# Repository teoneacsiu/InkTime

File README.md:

# InkTime

Smartwatch open-source bazat pe **nRF52840**, proiectat pentru cursul TSC. Acest repository contine partea de hardware, manufacturing si integrare mecanica pentru varianta **InkTime**.

---

## Structura repository-ului

```text
Hardware/
  - schematic (.sch)
  - board (.brd)

Manufacturing/
  - gerbers.zip
  - Bill of Materials (.bom / .csv)
  - Pick and Place (.cpl)

Mechanical/
  - ansamblu complet (.step)
  - fisierul Fusion360 al ansamblului complet

Images/
  - randari PCB
  - randari assembly
  - capturi schematic / board

LICENSE
README.md
```

---

## Stare proiect

- [x] structura repo
- [x] README completat
- [x] BOM de documentatie pentru componentele critice
- [x] schematic complet
- [x] ERC curat
- [x] board complet
- [x] DRC cu fisierul oficial
- [x] gerbers / BOM / CPL exportate
- [ ] model 3D complet: PCB + baterie + display + shaker + carcasa
- [ ] review DVT
- [ ] fix-uri pentru GNG

---

## Block diagram

```mermaid
flowchart LR
    USB[USB-C]
    ESD[USB ESD Protection]
    PMIC[BQ25180YBGR\nLi-Ion Charger + Power Path]
    DCDC[RT6160AWSC\nBuck-Boost 3V3]
    MCU[nRF52840\nBLE SoC]
    IMU[BMA421/BMA423\nAccelerometer]
    FG[MAX17048G+T10\nFuel Gauge]
    HAPTIC[DRV2605YZFR\nHaptic Driver]
    EPDPWR[E-Paper Power Stage]
    EPD[24-pin E-Paper FPC]
    BTN[3 Buttons]
    SWD[SWD Header / Test Pads]
    ANT[2.4 GHz Chip Antenna]
    BAT[Li-Po Battery]

    USB --> ESD --> MCU
    USB --> PMIC
    BAT --> PMIC
    BAT --> FG
    PMIC --> DCDC
    DCDC --> MCU
    DCDC --> IMU
    DCDC --> FG
    DCDC --> HAPTIC
    DCDC --> EPDPWR
    MCU <-->|I2C| IMU
    MCU <-->|I2C| PMIC
    MCU <-->|I2C| FG
    MCU <-->|I2C| HAPTIC
    MCU -->|SPI + control| EPDPWR
    EPDPWR --> EPD
    MCU --> BTN
    MCU --> SWD
    MCU --> ANT
```

---

## Arhitectura hardware

### 1. Microcontroller + radio
Controllerul principal este **nRF52840** in capsula QFN/AQFN, folosit pentru:
- controlul intregului sistem;
- comunicare BLE;
- interfata USB;
- I2C pentru PMIC / IMU / fuel gauge / haptic;
- SPI + semnale de control pentru display-ul e-paper;
- SWD pentru debug si programare.

Blocul radio foloseste:
- cristal de **32 MHz** pentru radio;
- cristal de **32.768 kHz** pentru timp real / low power;
- retea de adaptare RF;
- antena chip **2450AT18B100E**.

### 2. Alimentare
Alimentarea este impartita in doua etape:
- **BQ25180YBGR** pentru incarcarea bateriei Li-Po si power-path;
- **RT6160AWSC** pentru generarea tensiunii principale de **3V3**.

Aceasta separare permite:
- alimentare din USB;
- incarcare baterie;
- distributie stabila de 3V3 pentru MCU si periferice.

### 3. Senzori si periferice
- **BMA421/BMA423** - accelerometru low-power pentru detectie miscare / gesturi;
- **MAX17048G+T10** - fuel gauge pentru estimarea starii bateriei;
- **DRV2605YZFR** - driver haptic pentru feedback tactil;
- **E-paper connector + drive stage** - interfata catre display-ul principal;
- **3 butoane** - interfata fizica utilizator;
- **USB-C + ESD** - alimentare si comunicare USB.

---

## Interfete si mapare pini nRF52840

| Functie | Net / semnal | Pin nRF52840 | Motiv |
|---|---|---:|---|
| I2C data | SDA | P0.06 | magistrala comuna pentru PMIC, IMU, fuel gauge, haptic |
| I2C clock | SCL | P0.07 | magistrala comuna pentru PMIC, IMU, fuel gauge, haptic |
| PMIC interrupt | PMIC_INT | P0.11 | evenimente incarcare / power-path |
| IMU interrupt 1 | IMU_INT1 | P0.08 | semnal de intrerupere de la accelerometru |
| IMU interrupt 2 | IMU_INT2 | P1.08 | al doilea semnal de intrerupere de la accelerometru |
| Haptic enable / trigger | HAPTIC_EN | P0.12 | controlul driverului DRV2605 |
| Fuel gauge alert | ALERT | P0.10 / NFC2 | semnal alerta baterie / SOC |
| USB VBUS detect | VBUS | VBUS pin dedicat | detectare prezenta USB |
| USB data minus | D- | D- pin dedicat | USB 2.0 |
| USB data plus | D+ | D+ pin dedicat | USB 2.0 |
| Display chip select | EPD_CS | P0.05 | selectare SPI pentru e-paper |
| Display data/command | EPD_DC | P0.15 | diferentiere date/comenzi |
| Display busy | EPD_BUSY | P0.16 | status busy din display |
| Display reset | EPD_RST | P0.17 | reset hardware display |
| User button UP | SW_UP | P1.15 | input utilizator |
| User button ENTER | SW_ENT | P0.14 | input utilizator |
| User button DOWN | SW_DN | P1.02 | input utilizator |
| E-paper power enable | GPIO pentru Q1 | P1.01 | comanda alimentarea blocului e-paper |
| SWD data | SWDIO | SWDIO pin dedicat | debug/programare |
| SWD clock | SWDCLK | SWDCLK pin dedicat | debug/programare |
| Trace / debug | SWO | GPIO debug | punct de test pentru debugging |

### Observatii pe maparea pinilor
- Magistrala **I2C** este comuna si reduce numarul total de pini ocupati.
- Interfata USB foloseste pinii dedicati ai nRF52840 pentru compatibilitate corecta.
- Semnalele catre e-paper sunt separate intre control (`EPD_CS`, `EPD_DC`, `EPD_RST`, `EPD_BUSY`) si alimentare.
- Butoanele sunt conectate pe GPIO-uri separate pentru tratare simpla in firmware.
- Semnalele de debug sunt expuse atat prin conectorul SWD, cat si prin test pad-uri.

---

## Functionalitatea fiecarui bloc

### nRF52840
- MCU principal;
- BLE;
- USB FS;
- interfete I2C / SPI / GPIO;
- control low-power.

### BQ25180YBGR
- incarcare baterie Li-Ion/LiPo;
- power-path management;
- monitorizare si configurare prin I2C.

### RT6160AWSC
- buck-boost I2C-programmable;
- genereaza 3V3 din sursa sistemului;
- mentine tensiunea stabila pentru subsisteme.

### BMA421/BMA423
- accelerometru digital ultra-low-power;
- detectare miscare / activitate;
- intreruperi dedicate catre MCU.

### MAX17048G+T10
- fuel gauge pentru baterie LiPo;
- masoara tensiunea si estimeaza state-of-charge;
- alerta low battery catre MCU.

### DRV2605YZFR
- driver haptic pentru actuator ERM/LRA;
- controlabil prin I2C;
- permite feedback tactil complex.

### USB-C + ESD
- alimentare si date USB;
- rezistente de configurare CC;
- protectie ESD pe D+/D-/VBUS.

### E-paper drive + connector
- conector FPC de 24 pini;
- etapa de alimentare si comanda pentru display;
- linii SPI/control catre MCU.

---

## BOM de documentatie

BOM-ul de mai jos contine **componentele critice**. Pentru BOM-ul complet de productie trebuie folosit exportul din Fusion/EAGLE.

| RefDes | Componenta | MPN | Qty | Observatii |
|---|---|---|---:|---|
| U1 | BLE SoC | NRF52840-QIAA-R / QIAA-T | 1 | MCU principal |
| IC1 | Charger + power path | BQ25180YBGR | 1 | management baterie |
| IC9 | Buck-boost converter | RT6160AWSC | 1 | 3V3 principal |
| IC3 | IMU | BMA421 / BMA423 | 1 | biblioteca folosita contine BMA423 |
| U3 | Fuel gauge | MAX17048G+T10 | 1 | monitorizare baterie |
| IC2 | Haptic driver | DRV2605YZFR | 1 | control vibratii |
| J4 | USB-C | KH-TYPE-C-16P | 1 | alimentare + USB |
| D3 | ESD USB | USBLC6-2SC6Y | 1 | protectie D+/D-/VBUS |
| J1 | E-paper FPC | 503480-2400 | 1 | conector display |
| ANT1 | Chip antenna 2.4 GHz | 2450AT18B100E | 1 | BLE antenna |
| J2 | SWD header | TC2030-IDC | 1 | programare / debug |
| D2,D4,D5 | Schottky diode | MBR0530 | 3 | bloc power e-paper |
| Q3 | N-MOS | SI1308EDL-T1-GE3 | 1 | drive e-paper |
| Q1 | P-MOS | DMG2305UX-7 | 1 | comutare alimentare e-paper |
| X1 | RF crystal | 32MHz | 1 | ceas radio |
| X2 | RTC crystal | 32.768kHz | 1 | low-power timing |
| L7 | Inductor DCDC | FTC252012SR47MBCA | 1 | buck-boost RT6160 |
| SW_UP, SW_ENT, SW_DN | Butoane tactile | TBD | 3 | verificare finala dupa layout |
| Battery | Li-Po battery | TBD | 1 | model 3D de desenat |
| Display | E-paper module | TBD | 1 | model 3D de desenat |
| Shaker | ERM/LRA actuator | TBD | 1 | model 3D de desenat |

### Observatii BOM
- Toate rezistentele sunt SMD 0201.
- Toate condensatoarele cu valori `<= 100nF` sunt SMD 0201.
- Condensatoarele cu valori `> 100nF` sunt 0402, cu exceptiile specificate explicit in schema.
- BOM-ul din README este un BOM de documentatie; BOM-ul final de productie va fi exportat direct din CAD.

---

## Design rules si constrangeri care trebuie respectate

### PCB / mechanical
- grosime PCB: **1.0 mm**;
- componentele se amplaseaza **exclusiv pe TOP**;
- rutarea poate fi pe TOP si BOTTOM;
- trebuie **plan de masa pe TOP si pe BOTTOM**;
- daca se folosesc 4 straturi, unul dintre straturile interne trebuie sa fie GND;
- PCB-ul trebuie sa intre in carcasa furnizata;
- USB-C, butoanele si conectorul display trebuie aliniate mecanic cu carcasa.

### RF
- antena trebuie plasata spre exteriorul placii;
- sub antena **nu se pune plan de masa**;
- sub antena **nu se routeaza semnale**;
- se recomanda via stitching in jurul planurilor de GND, in special in zona radio.

### Routing
- trasee de putere: **0.30 mm**;
- trasee de semnal: **minim 0.15 mm**;
- fara unghiuri de 90°;
- se evita vias pe traseele de putere, pe cat posibil;
- condensatoarele de 100nF trebuie puse cat mai aproape de pinii de alimentare.

### Verificari
- ERC obligatoriu;
- DRC obligatoriu cu fisierul de reguli din arhiva;
- eroarea **Only INPUT pins on NET ID** poate fi ignorata;
- erorile de **Dimension** cauzate de butoane si USB pot fi justificate conform cerintei.

### Silkscreen
- silkscreen-ul trebuie sa fie lizibil;
- pe silkscreen se pastreaza **numele componentelor**, nu valorile;
- test pad-urile trebuie marcate clar cu numele semnalelor.

---

## Packaging si reguli de selectie a pasivelor

Conform cerintei:
- toate rezistentele sunt SMD **0201**;
- condensatoarele cu valori **<= 100nF** sunt **0201**;
- condensatoarele cu valori **> 100nF** sunt **0402**, cu exceptiile specificate explicit in schema.

---

## Manufacturing outputs

La final, repository-ul trebuie sa contina:

### Hardware
- `InkTime.sch`
- `InkTime.brd`

### Manufacturing
- `gerbers.zip`
- `InkTime.bom` / `BOM.csv`
- `InkTime.cpl`

### Mechanical
- ansamblu complet `STEP`
- fisierul Fusion360 al ansamblului complet

### Images
- randare PCB top
- randare PCB bottom
- randare assembly complet
- capturi schematic / board

---

## Design log / decizii

### Decizii luate pana acum
- biblioteca utilizata: `InkTime_v5.lbr`;
- schema este implementata dupa modelul furnizat;
- pentru IMU se foloseste simbolul / footprint-ul disponibil in biblioteca (**BMA423**), urmand sa fie mentionat explicit in review si in BOM;
- BOM-ul din README este unul de documentatie; BOM-ul final de asamblare va fi exportat direct din CAD;
- retelele critice de alimentare si RF au fost pastrate compacte pentru a facilita routarea si respectarea constrangerilor de layout.

### Probleme / aspecte de urmarit
- verificarea disponibilitatii finale la JLC pentru toate componentele critice;
- confirmarea exacta a modelului de baterie, display si shaker;
- verificarea finala a footprint-urilor pentru componentele foarte mici (WLCSP / DSBGA / AQFN);
- justificarea eventualelor erori DRC/Dimension acceptate conform cerintei;
- completarea integrarii mecanice 3D a bateriei, display-ului si actuatorului haptic.

---

## Imagini

Imaginile finale vor fi puse in `Images/`:
- `pcb_top.png`
- `pcb_bottom.png`
- `assembly_render.png`
- `schematic_page1.png`
- `schematic_page2.png`

---

## Limitari curente

In momentul actual, partea de proiectare electrica si de PCB este considerata finalizata la nivel de documentatie, iar partea ramasa de completat este integrarea 3D completa:
- modelul 3D al bateriei;
- modelul 3D al display-ului e-paper;
- modelul 3D al shaker-ului;
- verificarea finala a ansamblului complet in carcasa.

Toate celelalte livrabile hardware si de manufacturing sunt pregatite la nivel de repository si documentatie.

---

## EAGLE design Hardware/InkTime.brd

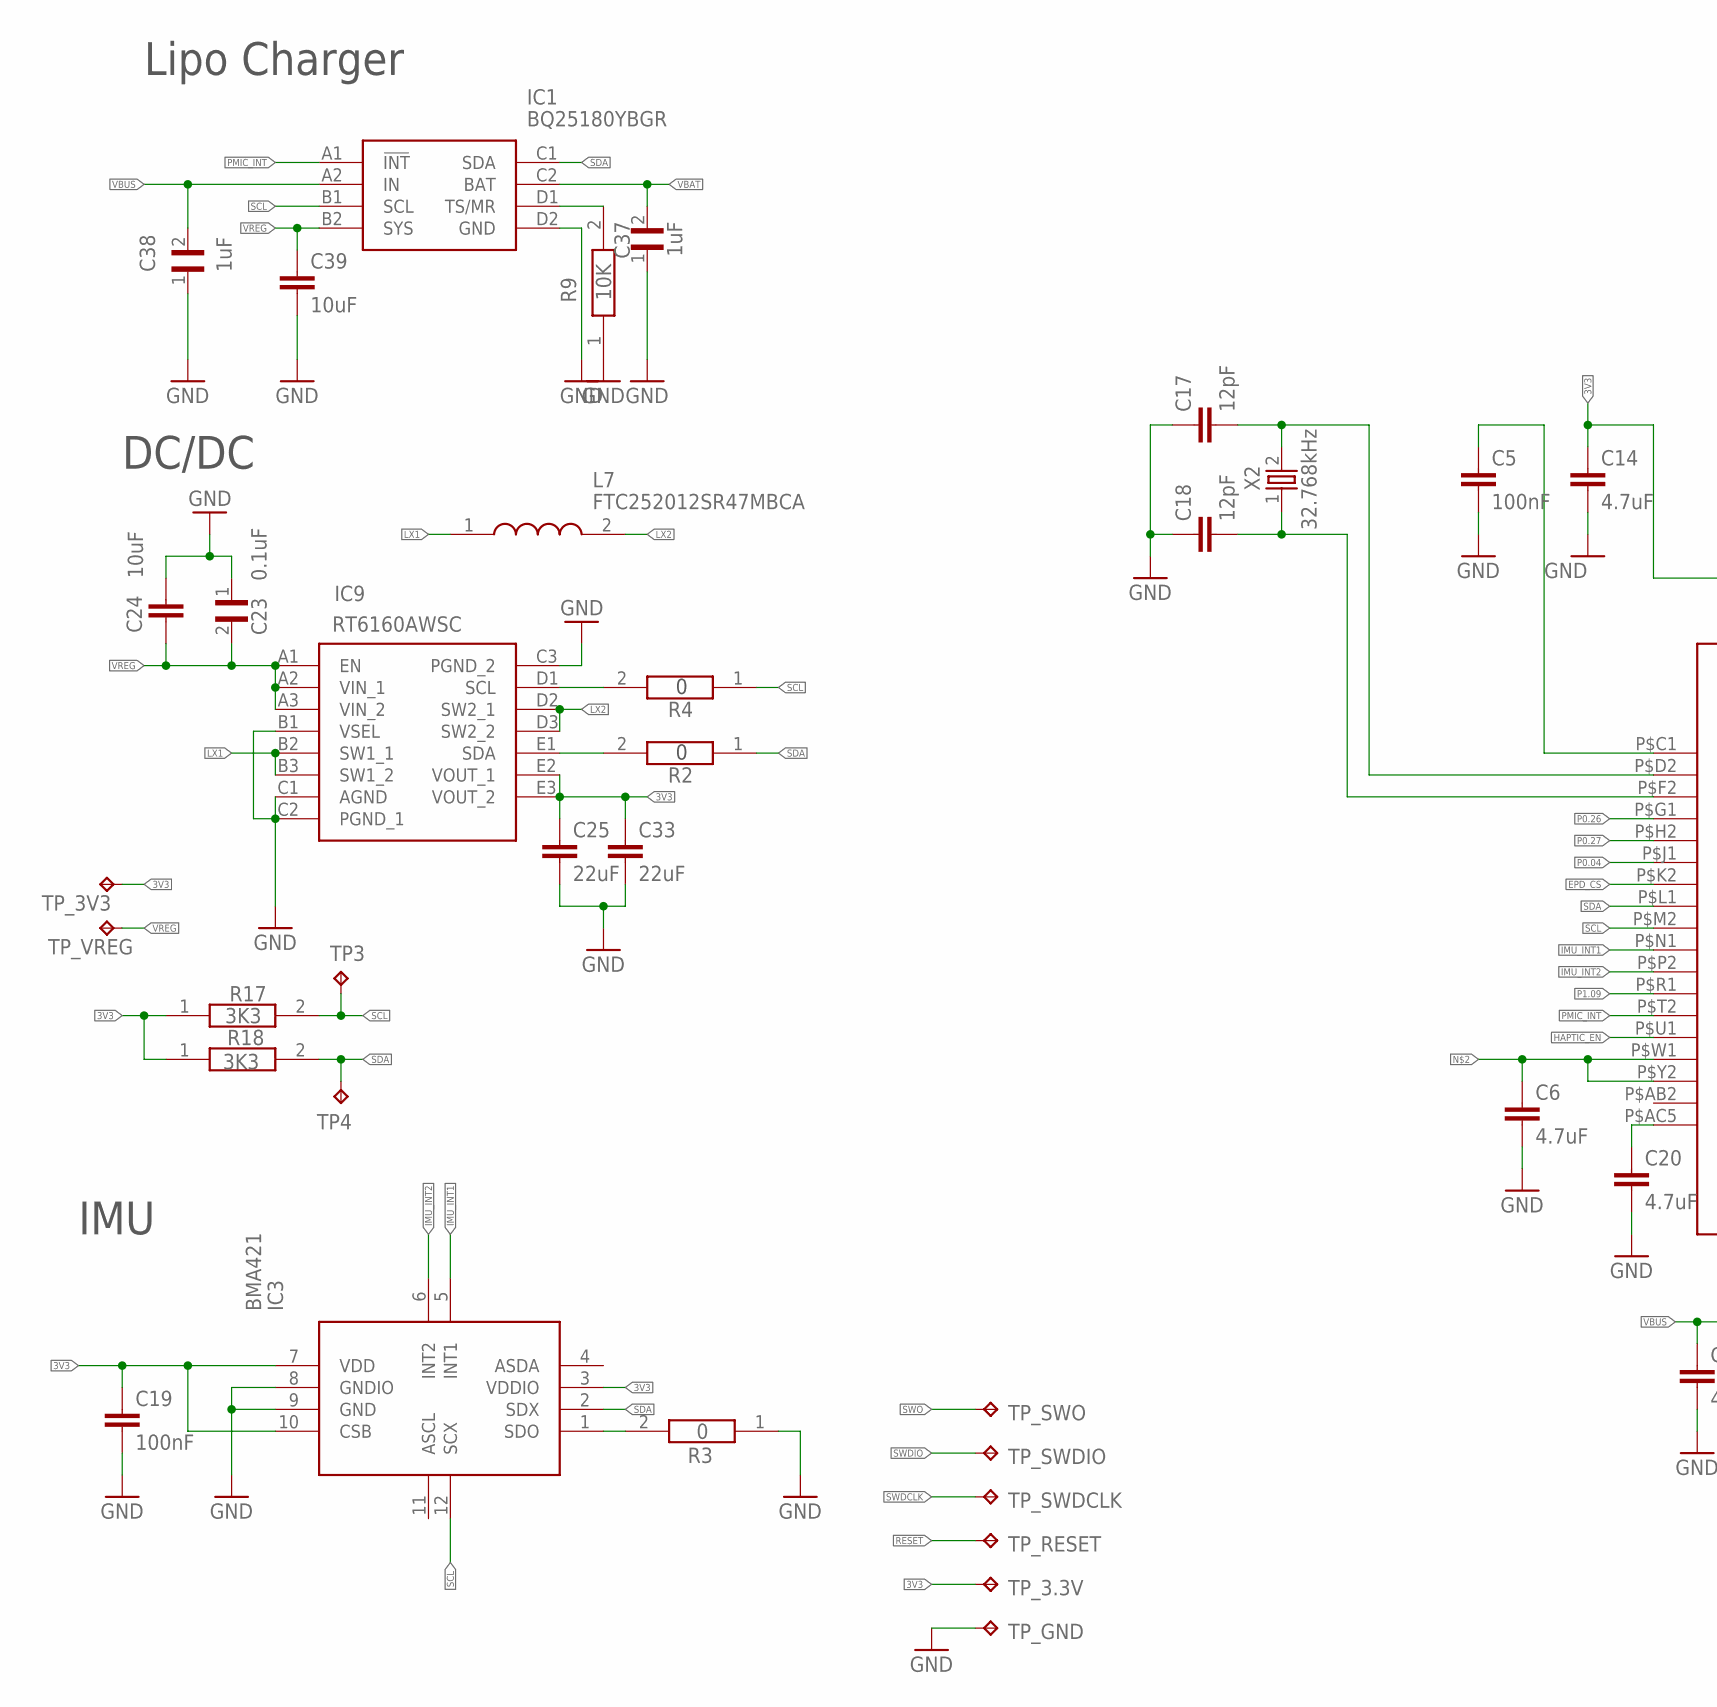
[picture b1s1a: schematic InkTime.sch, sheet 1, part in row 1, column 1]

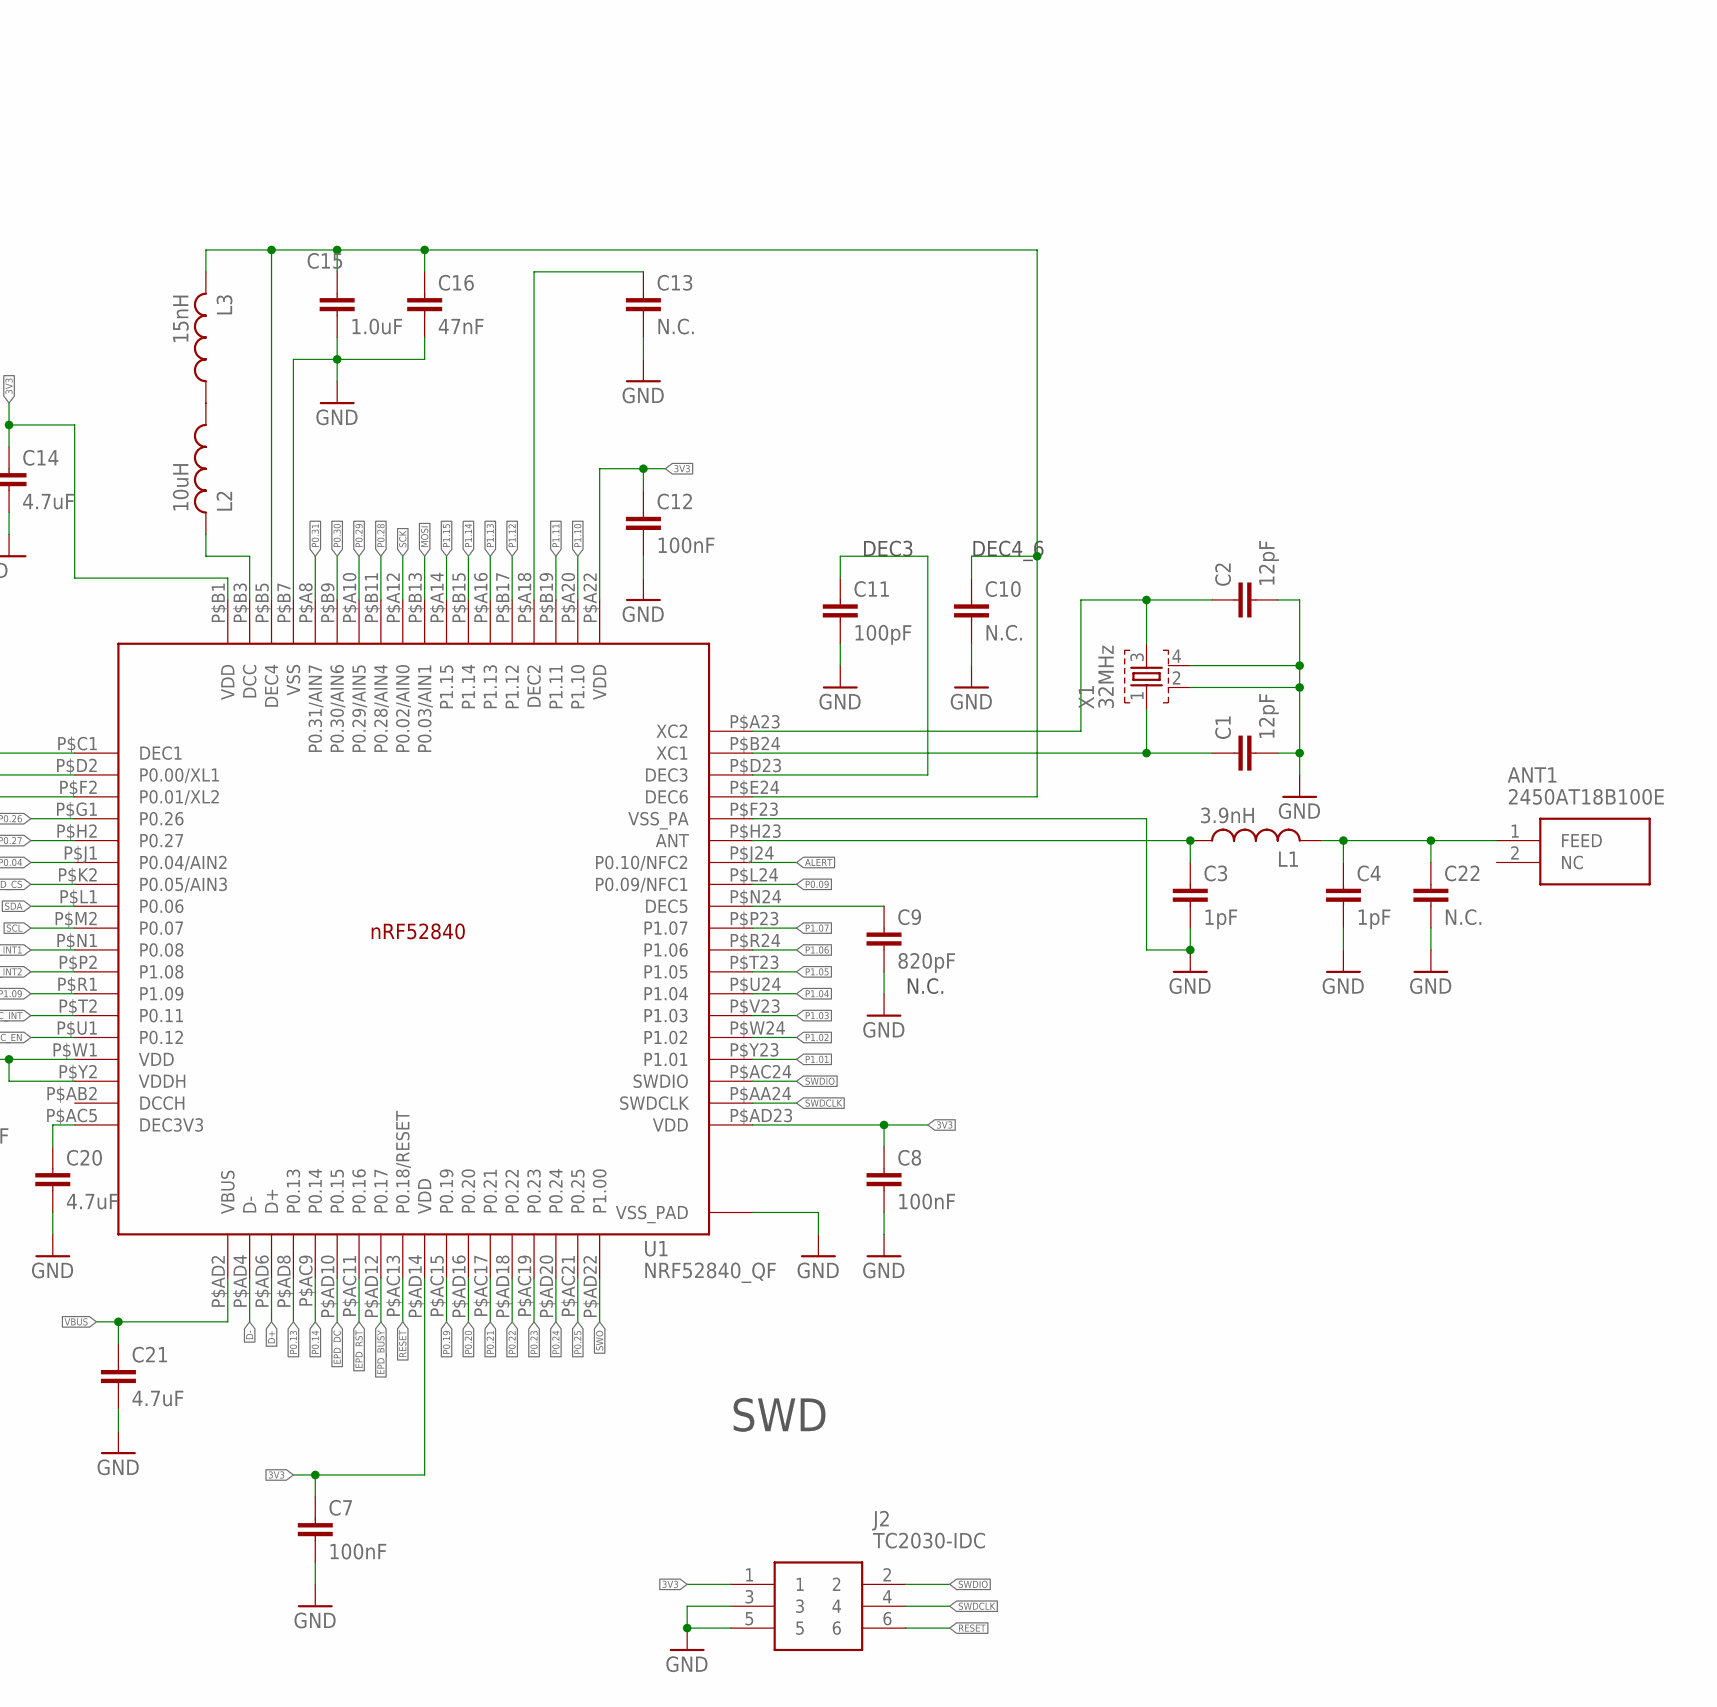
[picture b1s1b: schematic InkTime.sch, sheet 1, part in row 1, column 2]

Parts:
ANT1: 2450AT18B100E; 2450AT18B100E_ANTC3216X140N
C1, C2, C17, C18: 12pF; NORDIC_NRF_3_RESC0201_L
C3, C4: 1pF; NORDIC_NRF_3_RESC0201_L
C5, C7, C8, C12, C19: 100nF; NORDIC_NRF_3_RESC0402_L
C6, C14, C20, C21: 4.7uF; NORDIC_NRF_3_RESC0402_L
C9: 820pF; NORDIC_NRF_3_RESC0201_L
C10, C13, C22: N.C.; NORDIC_NRF_3_RESC0201_L
C11: 100pF; NORDIC_NRF_3_RESC0201_L
C15: 1.0uF; NORDIC_NRF_3_RESC0402_L
C16: 47nF; NORDIC_NRF_3_RESC0201_L
C23: 0.1uF; GRM011R60J152KE01L_2_CAPC0201X13N
C24: 10uF; NORDIC_NRF_3_RESC0201_L
C25, C33: 22uF; NORDIC_NRF_3_RESC0402_L
C37, C38: 1uF; GRM011R60J152KE01L_2_CAPC0201X13N
C39: 10uF; NORDIC_NRF_3_RESC0402_L
IC1: BQ25180YBGR; BQ25180YBGR_BGA8C40P2X4_100X155X50
IC3: BMA421; BMA423_BMA423
IC9: RT6160AWSC; RT6160AWSC_BGA15C40P3X5_140X230X60
J2: TC2030-IDC; TC2030-IDC_TC2030IDC
L1: 3.9nH; NORDIC_NRF_2_RESC0402_L
L2: 10uH; NORDIC_NRF_2_RESC0402_L
L3: 15nH; NORDIC_NRF_2_RESC0201_L
L7: FTC252012SR47MBCA; MLP2016SR47MT0S1_INDC2016X100N
R2, R4: 0; CPF0201D7K68C1_0201
R3: 0; ERA-1AEB3401C_0201
R9: 10K; CPF0201D7K68C1_0201
R17, R18: 3K3; CPF0201D7K68C1_0201
TP3, TP4: HECTOR_WATCH_1_TPTP20R; HECTOR_WATCH_1_TP20R
TP_3.3V, TP_3V3: HECTOR_WATCH_1_TPTP20R; HECTOR_WATCH_1_TP20R
TP_GND: HECTOR_WATCH_1_TPTP20R; HECTOR_WATCH_1_TP20R
TP_RESET: HECTOR_WATCH_1_TPTP20R; HECTOR_WATCH_1_TP20R
TP_SWDCLK: HECTOR_WATCH_1_TPTP20R; HECTOR_WATCH_1_TP20R
TP_SWDIO: HECTOR_WATCH_1_TPTP20R; HECTOR_WATCH_1_TP20R
TP_SWO: HECTOR_WATCH_1_TPTP20R; HECTOR_WATCH_1_TP20R
TP_VREG: HECTOR_WATCH_1_TPTP20R; HECTOR_WATCH_1_TP20R
U1: NRF52840_QF; NORDIC_NRF_4_AQFN50P700X700X85_HS-74N
X1: 32MHz; NORDIC_NRF_BT-XTAL_2016_N
X2: 32.768kHz; NORDIC_NRF_1_XTAL_3215_N

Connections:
3V3: C7.1, C8.1, C12.1, C14.1, C19.1, C25.1, C33.1, IC3.3 (VDDIO), IC3.7 (VDD), IC3.10 (CSB), IC9.E2 (VOUT_1), IC9.E3 (VOUT_2), J2.1, R17.1, R18.1, TP_3.3V.TP, TP_3V3.TP, U1.P$A22 (VDD), U1.P$AD14 (VDD), U1.P$AD23 (VDD), U1.P$B1 (VDD); also elsewhere on the board
ALERT: U1.P$J24 (P0.10/NFC2); also elsewhere on the board
D+: U1.P$AD6 (D+); also elsewhere on the board
D-: U1.P$AD4 (D-); also elsewhere on the board
EPD_BUSY: U1.P$AD12 (P0.17); also elsewhere on the board
EPD_CS: U1.P$K2 (P0.05/AIN3); also elsewhere on the board
EPD_DC: U1.P$AD10 (P0.15); also elsewhere on the board
EPD_RST: U1.P$AC11 (P0.16); also elsewhere on the board
GND: C1.2, C2.2, C3.2, C4.2, C5.2, C6.2, C7.2, C8.2, C9.2, C10.2, C11.2, C12.2, C13.2, C14.2, C15.2, C16.2, C17.1, C18.1, C19.2, C20.2, C21.2, C22.2, C23.1, C24.1, C25.2, C33.2, C37.1, C38.1, C39.2, IC1.D2 (GND), IC3.8 (GNDIO), IC3.9 (GND), IC9.B1 (VSEL), IC9.C1 (AGND), IC9.C2 (PGND_1), IC9.C3 (PGND_2), J2.3, J2.5, R3.1, R9.1, TP_GND.TP, U1.P$74 (VSS_PAD), U1.P$75 (VSS_PAD), U1.P$76 (VSS_PAD), U1.P$77 (VSS_PAD), U1.P$78 (VSS_PAD), U1.P$79 (VSS_PAD), U1.P$80 (VSS_PAD), U1.P$81 (VSS_PAD), U1.P$82 (VSS_PAD), U1.P$83 (VSS_PAD), U1.P$84 (VSS_PAD), U1.P$85 (VSS_PAD), U1.P$86 (VSS_PAD), U1.P$87 (VSS_PAD), U1.P$88 (VSS_PAD), U1.P$89 (VSS_PAD), U1.P$90 (VSS_PAD), U1.P$B7 (VSS), U1.P$F23 (VSS_PA), X1.2, X1.4; also elsewhere on the board
HAPTIC_EN: U1.P$U1 (P0.12); also elsewhere on the board
IMU_INT1: IC3.5 (INT1), U1.P$N1 (P0.08)
IMU_INT2: IC3.6 (INT2), U1.P$P2 (P1.08)
LX1: IC9.B2 (SW1_1), IC9.B3 (SW1_2), L7.1
LX2: IC9.D2 (SW2_1), IC9.D3 (SW2_2), L7.2
MOSI: U1.P$B13 (P0.03/AIN1); also elsewhere on the board
unnamed: IC1.D1 (TS/MR), R9.2
unnamed: C6.1, U1.P$W1 (VDD), U1.P$Y2 (VDDH)
unnamed: C17.2, U1.P$D2 (P0.00/XL1), X2.2
unnamed: C20.1, U1.P$AC5 (DEC3V3)
unnamed: C18.2, U1.P$F2 (P0.01/XL2), X2.1
unnamed: C5.1, U1.P$C1 (DEC1)
unnamed: IC9.D1 (SCL), R4.2
unnamed: ANT1.1 (FEED), C4.1, C22.1, L1.2
unnamed: IC9.E1 (SDA), R2.2
unnamed: L2.2, U1.P$B3 (DCC)
unnamed: C13.1, U1.P$A18 (DEC2)
unnamed: C2.1, U1.P$A23 (XC2), X1.3
unnamed: C1.1, U1.P$B24 (XC1), X1.1
unnamed: C11.1, U1.P$D23 (DEC3)
unnamed: C10.1, C15.1, C16.1, L3.2, U1.P$B5 (DEC4), U1.P$E24 (DEC6)
unnamed: C3.1, L1.1, U1.P$H23 (ANT)
unnamed: C9.1, U1.P$N24 (DEC5)
unnamed: IC3.1 (SDO), R3.2
unnamed: L2.1, L3.1
P0.04: U1.P$J1 (P0.04/AIN2)
P0.09: U1.P$L24 (P0.09/NFC1)
P0.13: U1.P$AD8 (P0.13); also elsewhere on the board
P0.14: U1.P$AC9 (P0.14); also elsewhere on the board
P0.19: U1.P$AC15 (P0.19)
P0.20: U1.P$AD16 (P0.20)
P0.21: U1.P$AC17 (P0.21)
P0.22: U1.P$AD18 (P0.22)
P0.23: U1.P$AC19 (P0.23)
P0.24: U1.P$AD20 (P0.24)
P0.25: U1.P$AC21 (P0.25)
P0.26: U1.P$G1 (P0.26)
P0.27: U1.P$H2 (P0.27)
P0.28: U1.P$B11 (P0.28/AIN4)
P0.29: U1.P$A10 (P0.29/AIN5)
P0.30: U1.P$B9 (P0.30/AIN6)
P0.31: U1.P$A8 (P0.31/AIN7)
P1.01: U1.P$Y23 (P1.01); also elsewhere on the board
P1.02: U1.P$W24 (P1.02); also elsewhere on the board
P1.03: U1.P$V23 (P1.03)
P1.04: U1.P$U24 (P1.04)
P1.05: U1.P$T23 (P1.05)
P1.06: U1.P$R24 (P1.06)
P1.07: U1.P$P23 (P1.07)
P1.09: U1.P$R1 (P1.09)
P1.10: U1.P$A20 (P1.10)
P1.11: U1.P$B19 (P1.11)
P1.12: U1.P$B17 (P1.12)
P1.13: U1.P$A16 (P1.13)
P1.14: U1.P$B15 (P1.14)
P1.15: U1.P$A14 (P1.15)
PMIC_INT: IC1.A1 (!INT), U1.P$T2 (P0.11)
RESET: J2.6, TP_RESET.TP, U1.P$AC13 (P0.18/RESET)
SCK: U1.P$A12 (P0.02/AIN0); also elsewhere on the board
SCL: IC1.B1 (SCL), IC3.12 (SCX), R4.1, R17.2, TP3.TP, U1.P$M2 (P0.07); also elsewhere on the board
SDA: IC1.C1 (SDA), IC3.2 (SDX), R2.1, R18.2, TP4.TP, U1.P$L1 (P0.06); also elsewhere on the board
SWDCLK: J2.4, TP_SWDCLK.TP, U1.P$AA24 (SWDCLK)
SWDIO: J2.2, TP_SWDIO.TP, U1.P$AC24 (SWDIO)
SWO: TP_SWO.TP, U1.P$AD22 (P1.00)
VBAT: C37.2, IC1.C2 (BAT); also elsewhere on the board
VBUS: C21.1, C38.2, IC1.A2 (IN), U1.P$AD2 (VBUS); also elsewhere on the board
VREG: C23.2, C24.2, C39.1, IC1.B2 (SYS), IC9.A1 (EN), IC9.A2 (VIN_1), IC9.A3 (VIN_2), TP_VREG.TP

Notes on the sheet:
Lipo Charger
N.C.
DC/DC
IMU
DEC3
DEC4_6
SWD

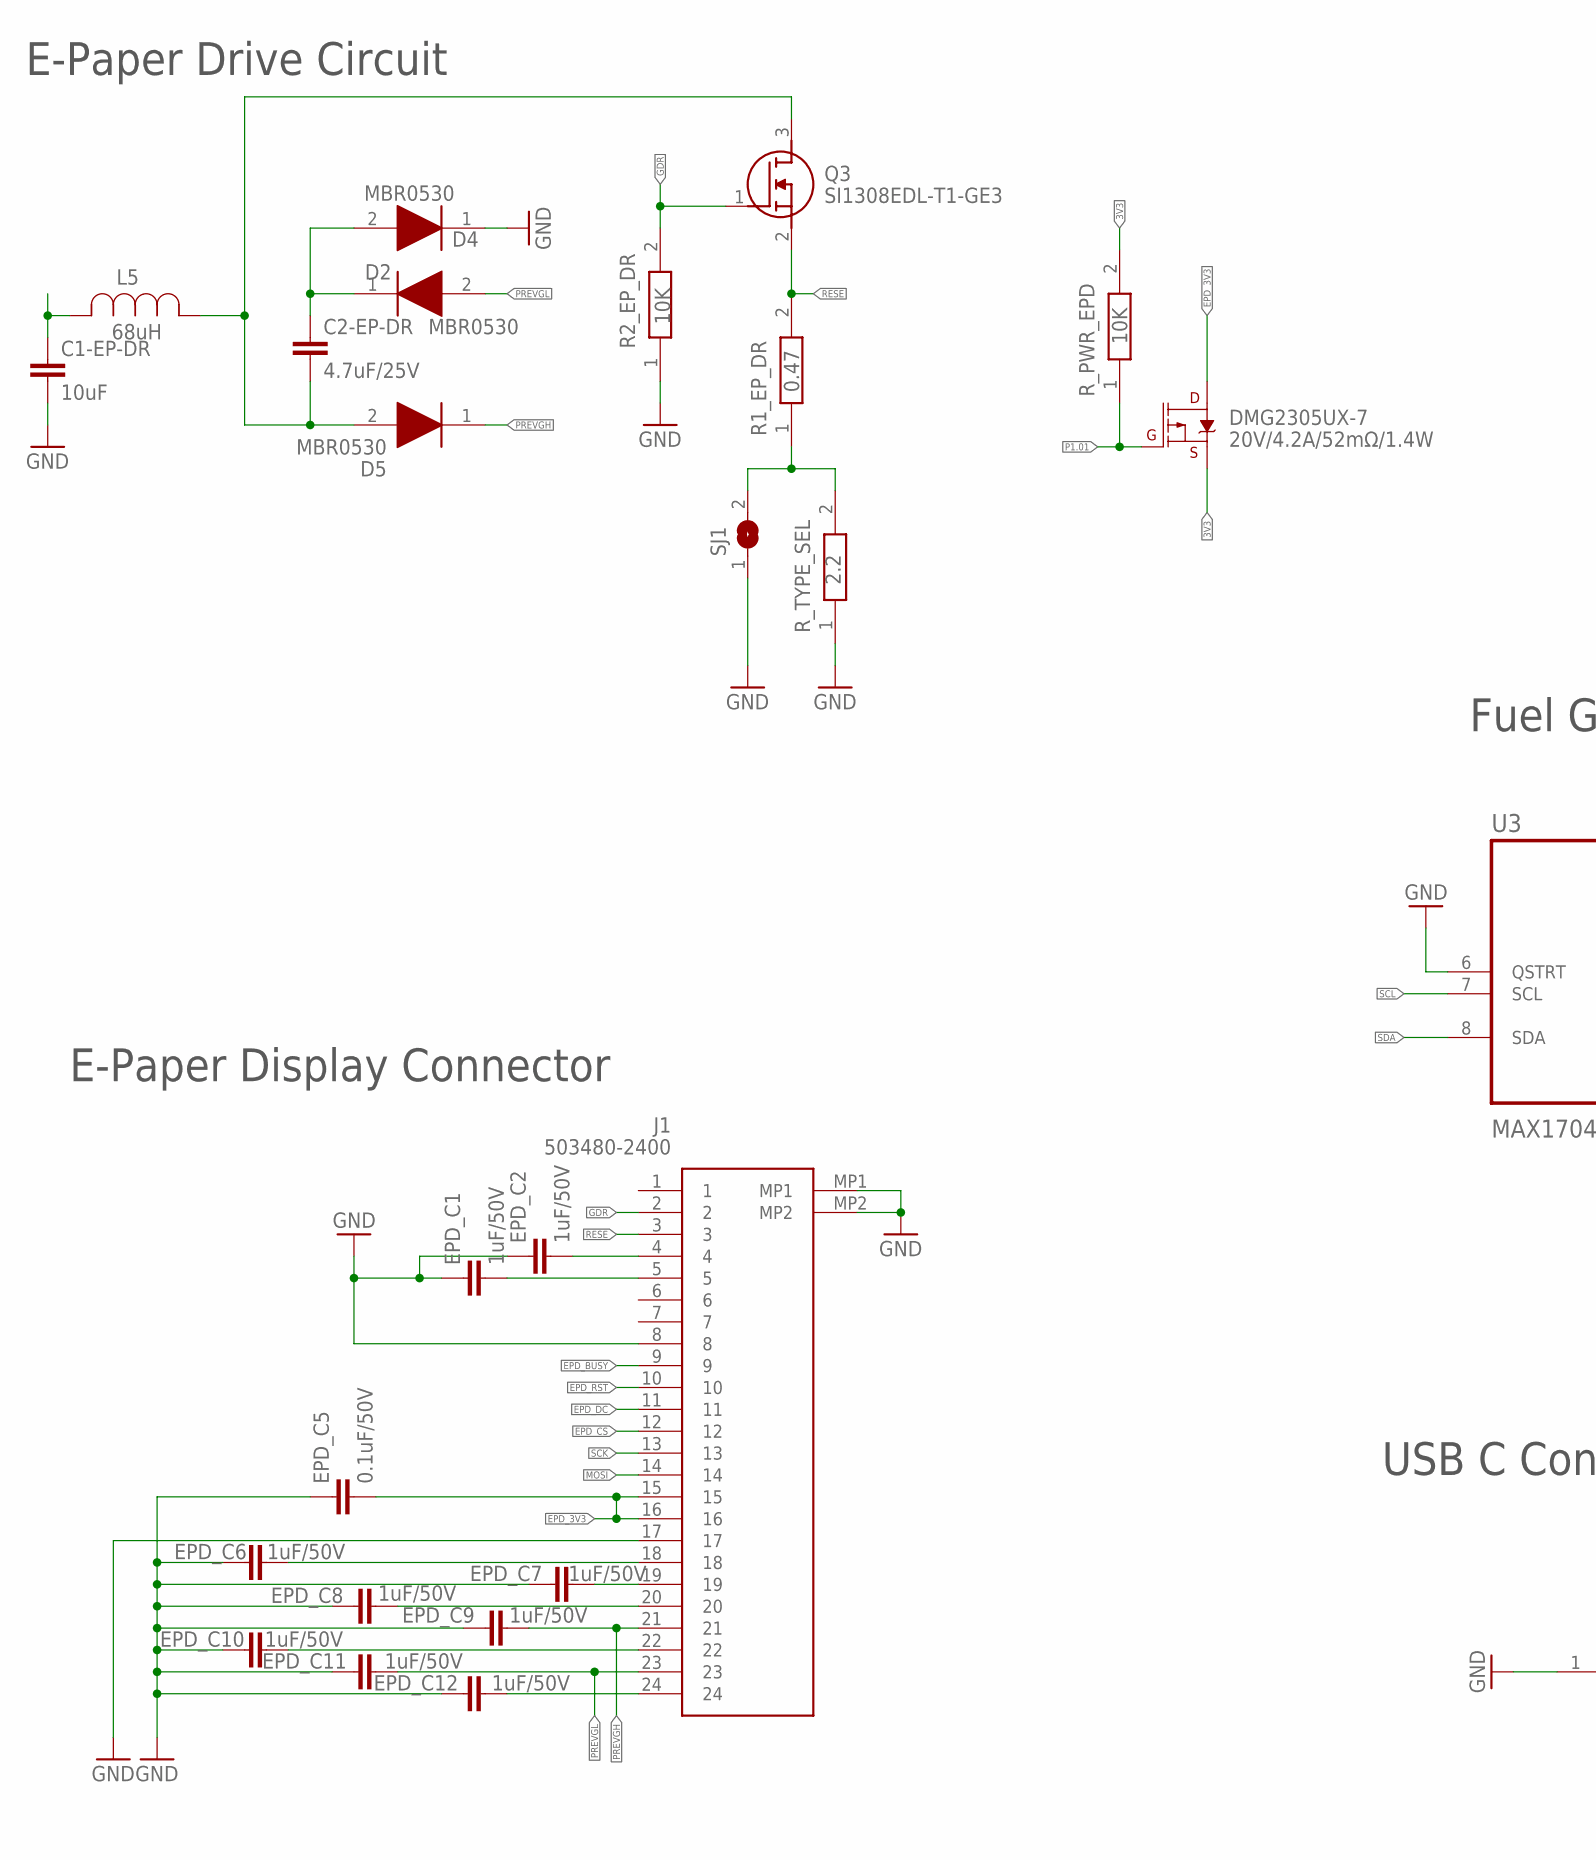
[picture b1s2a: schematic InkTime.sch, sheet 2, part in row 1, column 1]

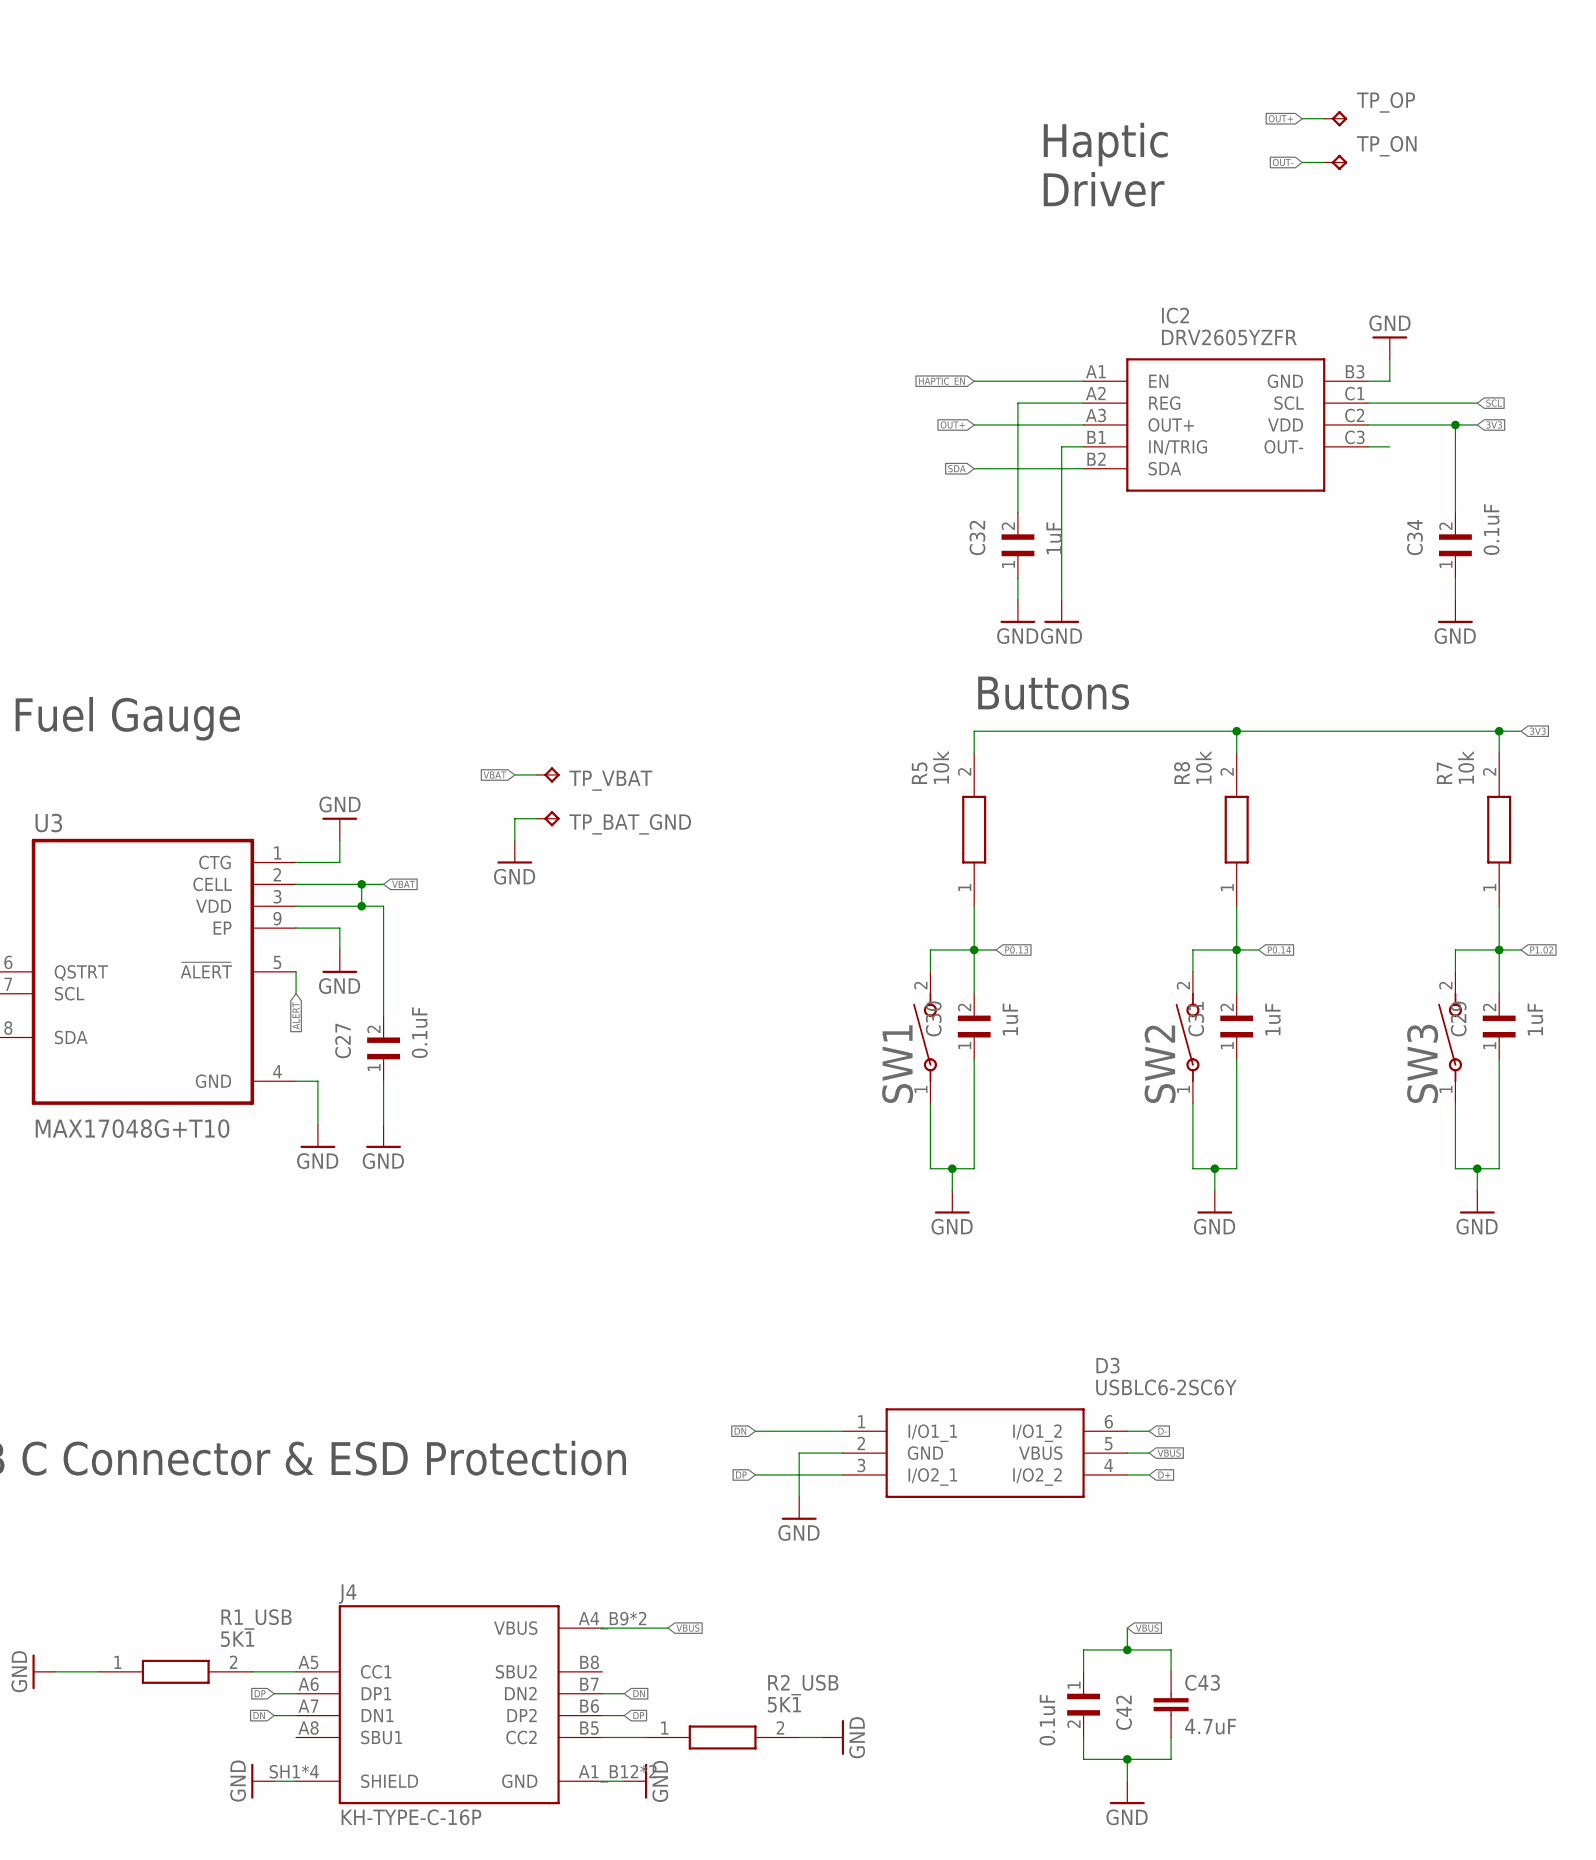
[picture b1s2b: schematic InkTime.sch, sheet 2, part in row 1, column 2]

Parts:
C1-EP-DR: 10uF; NORDIC_NRF_3_RESC0402_L
C2-EP-DR: 4.7uF/25V; NORDIC_NRF_3_RESC0402_L
C27, C34, C42: 0.1uF; GRM011R60J152KE01L_2_CAPC0201X13N
C29, C30, C31, C32: 1uF; GRM011R60J152KE01L_2_CAPC0201X13N
C43: 4.7uF; NORDIC_NRF_3_RESC0402_L
D2, D4, D5: MBR0530; ESP32_C6_LIBRARY_5_SOD3716X135N
D3: USBLC6-2SC6Y; ESP32_C6_LIBRARY_3_SOT95P280X145-6N
DMG2305UX-7: 20V/4.2A/52mΩ/1.4W; ESP32_C6_LIBRARY_4_ESP32_C6_LIBRARY_4_ESP32_C6_LIBRARY_4_ES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
EPD_C1, EPD_C2, EPD_C6, EPD_C7, EPD_C8, EPD_C9, EPD_C10, EPD_C11, EPD_C12: 1uF/50V; NORDIC_NRF_3_RESC0402_L
EPD_C5: 0.1uF/50V; NORDIC_NRF_3_RESC0402_L
IC2: DRV2605YZFR; DRV2605YZFR_BGA9C50P3X3_144X144X62
J1: 503480-2400; 503480-2400_5034802400
J4: KH-TYPE-C-16P; KH-TYPE-C-16P_KINGHELM_KH-TYPE-C-16P
L5: 68uH; ESP32_C6_LIBRARY_2_IND_4828-WE-TPC_WRE
Q3: SI1308EDL-T1-GE3; ESP32_C6_LIBRARY_6_SOT65P210X110-3N
R1_EP_DR: 0.47; CPF0201D7K68C1_0201
R1_USB, R2_USB: 5K1; CPF0201D7K68C1_0201
R2_EP_DR: 10K; CPF0201D7K68C1_0201
R5, R7, R8: 10k; CPF0201D7K68C1_0201
R_PWR_EPD: 10K; CPF0201D7K68C1_0201
R_TYPE_SEL: 2.2; CPF0201D7K68C1_0201
SJ1: ESP32_C6_LIBRARY_7_JUMPER_SJ
SW1, SW2, SW3: 2025-10-22_07-23-44_LIBRARY_EVP-AKE31ASW_EVP-AKE3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; 2025-10-22_07-23-44_LIBRARY_SW_EVP-AKE31A_PAN
TP_BAT_GND: HECTOR_WATCH_1_TPTP20R; HECTOR_WATCH_1_TP20R
TP_ON: HECTOR_WATCH_1_TPTP20R; HECTOR_WATCH_1_TP20R
TP_OP: HECTOR_WATCH_1_TPTP20R; HECTOR_WATCH_1_TP20R
TP_VBAT: HECTOR_WATCH_1_TPTP20R; HECTOR_WATCH_1_TP20R
U3: MAX17048G+T10; ESP32_C6_LIBRARY_SON50P200X200X80-9N

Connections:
3V3: C34.2, DMG2305UX-7.2 (S), IC2.C2 (VDD), R5.2, R7.2, R8.2, R_PWR_EPD.2; also elsewhere on the board
ALERT: U3.5 (!ALERT); also elsewhere on the board
D+: D3.4 (I/O2_2); also elsewhere on the board
D-: D3.6 (I/O1_2); also elsewhere on the board
DN: D3.1 (I/O1_1), J4.A7 (DN1), J4.B7 (DN2)
DP: D3.3 (I/O2_1), J4.A6 (DP1), J4.B6 (DP2)
EPD_3V3: DMG2305UX-7.3 (D), EPD_C5.2, J1.15, J1.16
EPD_BUSY: J1.9; also elsewhere on the board
EPD_CS: J1.12; also elsewhere on the board
EPD_DC: J1.11; also elsewhere on the board
EPD_RST: J1.10; also elsewhere on the board
GDR: J1.2, Q3.1 (G), R2_EP_DR.2
GND: C1-EP-DR.2, C27.1, C29.1, C30.1, C31.1, C32.1, C34.1, C42.2, C43.2, D3.2 (GND), D4.1 (K), EPD_C1.1, EPD_C2.1, EPD_C5.1, EPD_C6.1, EPD_C7.2, EPD_C8.2, EPD_C9.2, EPD_C10.1, EPD_C11.2, EPD_C12.2, IC2.B1 (IN/TRIG), IC2.B3 (GND), J1.8, J1.17, J1.MP1, J1.MP2, J4.A1_B12 (GND), J4.A12_B1 (GND), J4.SH1 (SHIELD), J4.SH2 (SHIELD), J4.SH3 (SHIELD), J4.SH4 (SHIELD), R1_USB.1, R2_EP_DR.1, R2_USB.2, R_TYPE_SEL.1, SJ1.1, SW1.1, SW2.1, SW3.1, TP_BAT_GND.TP, U3.1 (CTG), U3.4 (GND), U3.6 (QSTRT), U3.9 (EP); also elsewhere on the board
HAPTIC_EN: IC2.A1 (EN); also elsewhere on the board
MOSI: J1.14; also elsewhere on the board
unnamed: C1-EP-DR.1, L5.2
unnamed: C2-EP-DR.2, D5.2 (A), L5.1, Q3.3 (D)
unnamed: C2-EP-DR.1, D2.1 (K), D4.2 (A)
unnamed: R1_EP_DR.1, R_TYPE_SEL.2, SJ1.2
unnamed: EPD_C2.2, J1.4
unnamed: EPD_C1.2, J1.5
unnamed: EPD_C6.2, J1.18
unnamed: EPD_C7.1, J1.19
unnamed: EPD_C8.1, J1.20
unnamed: C32.2, IC2.A2 (REG)
unnamed: J4.A5 (CC1), R1_USB.2
unnamed: EPD_C10.2, J1.22
unnamed: EPD_C12.1, J1.24
unnamed: J4.B5 (CC2), R2_USB.1
OUT+: IC2.A3 (OUT+), TP_OP.TP
OUT-: TP_ON.TP
P0.13: C30.2, R5.1, SW1.2; also elsewhere on the board
P0.14: C31.2, R8.1, SW2.2; also elsewhere on the board
P1.01: DMG2305UX-7.1 (G), R_PWR_EPD.1; also elsewhere on the board
P1.02: C29.2, R7.1, SW3.2; also elsewhere on the board
PREVGH: D5.1 (K), EPD_C9.1, J1.21
PREVGL: D2.2 (A), EPD_C11.1, J1.23
RESE: J1.3, Q3.2 (S), R1_EP_DR.2
SCK: J1.13; also elsewhere on the board
SCL: IC2.C1 (SCL), U3.7 (SCL); also elsewhere on the board
SDA: IC2.B2 (SDA), U3.8 (SDA); also elsewhere on the board
VBAT: C27.2, TP_VBAT.TP, U3.2 (CELL), U3.3 (VDD); also elsewhere on the board
VBUS: C42.1, C43.1, D3.5 (VBUS), J4.A4_B9 (VBUS), J4.A9_B4 (VBUS); also elsewhere on the board

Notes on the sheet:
E-Paper Drive Circuit
Haptic Driver
E-Paper Display Connector
USB C Connector & ESD Protection
Fuel Gauge
Buttons

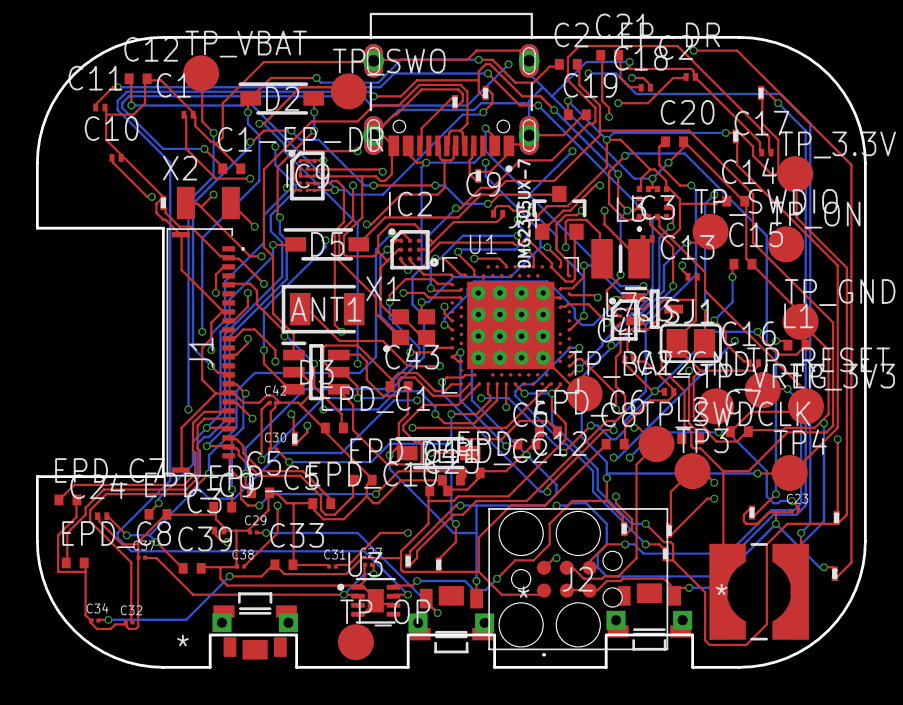
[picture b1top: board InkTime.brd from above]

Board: 4 copper layers, 46.0 x 35.0 mm, 105 parts (0 on the bottom side), 71 nets.

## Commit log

2026-04-18 Reparare
2026-04-21 Documentatie in plus
2026-04-22 STEP

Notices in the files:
parts and their libraries:
COPYRIGHT: Copyright (C) 2024 Ultra Librarian. All rights reserved.
COPYRIGHT: Copyright (C) 2025 Ultra Librarian. All rights reserved.
